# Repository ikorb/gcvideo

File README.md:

# GCVideo #

GCVideo is a small series of FPGA boards and VHDL projects
capable of converting the
GameCube's Digital Video port signals to standard video signals
without using the custom chip in the original component video cable.
There are currently VHDL projects for multiple FPGA boards, including
a Gamecube-to-DVI version for the KNJN Pluto IIx-HDMI and a
Gamecube-to-Component/RGB version for a board called GCVideo Lite
which is also documented in this repository.
GCVideo Lite has also been adapted to be used as
an RGB DAC for the Nintendo 64.

The schematics and layout are in the [Hardware](Hardware) directory
and the HDL projects are in the [HDL](HDL) directory. Each directory
should contain README.md files with further information.

## Mini-FAQ ##

1. I want one, how much is it?  
    I do not sell any hardware. Since this is an open-source project,
    other people will probably offer ready-made boards or modding
    services.

    GCVideo-DVI is based on a readily-available, commercial FPGA
    development board, so you could just buy that, flash it and
    install it yourself (or find someone to do it for you).

1. But why don't you just sell it?  
    Building hardware to be sold is a lot of work and requires much
    time that I'd rather use for something more
    interesting. Furthermore, the local laws require quite a bit of
    paperwork and investment to legally sell electronic devices that
    you build and I'd prefer not to deal with all of that.

1. You said your prototype came from OSHPark, so you have at least
    three boards. Can't you sell me one of them?  
    No, they're all accounted for already.

1. Why did you use that weird Video-DAC, it's a non-stock part at
    Digikey!<br>
    It wasn't when I designed the board some months ago... Instead it
    was the cheapest 24-bit video DAC available. It shouldn't be hard
    to adapt the design to a different DAC as long as it has 24 bit
    parallel input and a single-pumped clock. For YPbPr output, the
    DAC also needs to be able to generate a small offset on the Y line
    so that syncs can be generated below the blanking level.

1. Uh, it says XO2-256 in the schematic, but XO2-640 in the BOM. Which
    is the correct one?  
    The original plan was to use an XO2-256, but adding the color
    space conversion for RGB output increased the size of the design
    too much. It was left as an XO2-256 in the schematic to ensure
    only pins available on that chip are used, so a slightly cheaper
    Component-only version can be built.

1. What about line-doubling?  
    GCVideo Lite (the analog version) uses the smallest FPGA that
    could fit everything needed, but this chip does not have enough
    BlockRAM available to generate a line-doubled picture. It could be
    updated by using a larger, footprint-compatible FPGA, but since
    480i/576i are well-supported on component inputs and 240p/288p are
    rarely used by Gamecube titles this has not been attempted yet.

    GCVideo DVI fully supports line-doubling and can also overlay
    scanlines on the line-doubled picture if desired.

# Licence #

<pre>
Copyright (C) 2014-2021, Ingo Korb &lt;ingo@akana.de&gt;
All rights reserved.

Redistribution and use in source and binary forms, with or without
modification, are permitted provided that the following conditions are met:

1. Redistributions of source code must retain the above copyright notice,
   this list of conditions and the following disclaimer.
2. Redistributions in binary form must reproduce the above copyright notice,
   this list of conditions and the following disclaimer in the documentation
   and/or other materials provided with the distribution.

THIS SOFTWARE IS PROVIDED BY THE COPYRIGHT HOLDERS AND CONTRIBUTORS "AS IS"
AND ANY EXPRESS OR IMPLIED WARRANTIES, INCLUDING, BUT NOT LIMITED TO, THE
IMPLIED WARRANTIES OF MERCHANTABILITY AND FITNESS FOR A PARTICULAR PURPOSE
ARE DISCLAIMED. IN NO EVENT SHALL THE COPYRIGHT HOLDER OR CONTRIBUTORS BE
LIABLE FOR ANY DIRECT, INDIRECT, INCIDENTAL, SPECIAL, EXEMPLARY, OR
CONSEQUENTIAL DAMAGES (INCLUDING, BUT NOT LIMITED TO, PROCUREMENT OF
SUBSTITUTE GOODS OR SERVICES; LOSS OF USE, DATA, OR PROFITS; OR BUSINESS
INTERRUPTION) HOWEVER CAUSED AND ON ANY THEORY OF LIABILITY, WHETHER IN
CONTRACT, STRICT LIABILITY, OR TORT (INCLUDING NEGLIGENCE OR OTHERWISE)
ARISING IN ANY WAY OUT OF THE USE OF THIS SOFTWARE, EVEN IF ADVISED OF
THE POSSIBILITY OF SUCH DAMAGE.
</pre>

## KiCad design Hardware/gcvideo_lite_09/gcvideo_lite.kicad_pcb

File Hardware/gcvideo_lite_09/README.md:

# GCVideo Lite 0.9 #

This is the first prototype GCVideo Lite board with analog outputs in
RGB and Component/YPbPr formats, revision 0.9. This revision has a few
minor annoyances, but has proven to work.

## Connectors ##

The board has five connectors and one jumper: The main signal and
power input is the 11x2 connector P1 which connects to the GameCube
Digital Video port. The 6x1 connector on the side is the JTAG
connector which is needed to program the FPGA on the board. Signal
outputs are on the 5x1 and 4x1 connectors. There is also a 2x2
connector labelled "spare" next to the P1 and JTAG connectors which
at this time is mostly unused except for one pin that outputs an SPDIF
audio signal.

The single jumper on the board is located next to the JTAG connector
and consists of two solder pads. If these pads are bridged, the FPGA
will output RGB signals, if they are open it will output component
signals. 

### P1 (11x2) ###

The board is connected to the GameCube's digital video port using the
pins of the P1 connector. Since the original connector in the GameCube
is proprietary and no alternative is known, this needs to be done
using wires. It is strongly recommended to keep these wires as short
as possible since one of them is a 54MHz clock signal. Be absolutely
sure to not connect or bridge anything to pin 5 (+12V) - an accidental
short between that pin and any of the data lines will instantly fry
the Gamecube.

The pins of the P1 connector on the GCVideo Lite board correspond 1:1
with the pins of the GC's digital video connector, pin 1 is marked
with a square instead of a round pad. [This
site](http://gamesx.com/wiki/doku.php?id=av:nintendodigitalav) shows
the pin numbering directly on the connector. Alternatively, if you
look at the bottom of the GameCube's main PCB with the video
connectors facing away from you, pin 1 of the DV connector should be
the bottom right pin, pin 2 the one above it. There are also numbers
for the outermost pins marked besides the connector on the top side.

I have no idea what your options are if you have a later-model
GameCube where Nintendo removed the digital AV port.

### JTAG (6x1) ###

The FPGA has an internal configuration memory which is blank when it
is delivered from the factory. To program the FPGA, you need a
JTAG interface suitable for use with Lattice's software - I use a
clone of the HW-USBN-2A cable, but the software also supports a
parallel port cable (no idea about the pinout) or FT2232D-based USB
devices (look for Lattice application note AN8082 for the schematic).

On the software side, the FPGA can be programmed using the Lattice
Diamond software package. Although it may appear a bit large at about
1.5 GByte download size, this is quite small compared to similar
packages from other FPGA vendors. ;)
If programming the internal configuration flash of the XO2 fails, try
the .jed file instead of the .bit file.

### Video (5x1) ###

The video output connector is the 5x1 connector on the side of the
board. Pin 1 is marked using a square instead of a round pad and
outputs the R (RGB) or Pr (Component, red plug) signal. Pins 2 and 4
are ground pins. Pin 3 (the middle one) outputs the G (RGB) or Y
(Component, green plug) signal, Pin 5 outputs the B (RGB) or Pb
(Component, blue plug) signal. There is also a tiny label hidden
between the resistors and capacitors saying "B-G-R" which uses "-" as
a shorthand for ground.

### Sync (4x1) ###

The GCVideo Lite board has a dedicated connector for sync signals. You
can ignore it if you only want to output Component video, but it is
required if you want to use RGB. The pins are labelled "C V H -" on
the sikscreen. The "-" pin is ground, "V" and "H" are vertical and
horizontal sync signals and "C" is a composite sync signal. The
composite sync signal should be directly usable e.g. for connections
to SCART televisions or scalers like an XRGB Mini that need a
composite sync while the V- and H-Sync signals can be used for VGA
inputs - but remember that the GameCube outputs 15kHz video during
startup and not every game supports 480p!

While the hardware could support RGB with Sync-on-Green, this is
currently not implemented.

### Spare (2x2) ###

The 2x2 pin group marked "Spare" in the corner of the group is unused
except for the square pin next to P1. This pin is used to output an
SPDIF audio signal. For more information on interfacing this signal to
an SPDIF receiver, please check the [README.md of the gcvideo_lite HDL
project](../../HDL/gcvideo_lite/README.md).

Please do not connect this pin directly to a coaxial SPDIF input, the
feature was added after the board was designed and there is no
protection on this pin.

## Building ##

The PCB uses four layers, so it is not suitable for etching at home,
but there are many prototyping services available that offer small
runs of a PCB. The prototype has been ordered from
[OSHPark](http://www.oshpark.com) and the zip file with the data they
require has been included in the repository.

The values of the parts are marked within their footprint in rather
tiny letters, alternatively you can look at the [BOM.csv](BOM.csv)
file for the value corresponding to each of the component references.

## Audio ##

There are currently two options for the audio signal from the Gamecube
when GCVideo Lite is used as the video encoder. The first option is to
use the audio signals from the analog AV port as usual. The second
option is to use the SPDIF encoder implemented in GCVideo Lite. The
[README.md of the gcvideo_lite HDL
project](../../HDL/gcvideo_lite/README.md) has more information about
connecting this signal - since it was added after the board was
designed, no protection is present on the signal and a direct
connection to an SPDIF input may destroy the FPGA.

## Known issues ##

* The drill holes for the JTAG and output video/sync connectors are
    slightly too small to fit standard 2.54mm pitch pin headers.
* The pads of the two ICs (from KiCADs standard footprint library) are
    meant for reflow soldering, not hand soldering. It is still
    possdo not need to use ible to hand-solder these chips, but it takes a lot of
    patience.
* The "component cable connected" pin is always active, which causes
    some homebrew applications to switch into 480p mode by
    default. This can be problematic for users of SD-only monitors,
    but since the board must be connected to the cube using wires
    anyway, leaving out the connection of pin 1 (or adding a switch in
    that line) can fix this issue.
* Trace width could be increased for some of the supply traces on the
    top and bottom layers.
* Vias are a bit large-ish.

## Other Systems ##

With a different program in the FPGA it is be possible to use the
same board to provide RGB and/or Component outputs for an N64, see
the [gcvideo_lite_n64](../gcvideo_lite_n64/README.md) directory for
details.

Measurements on a Wii board indicate that thare is an internal video
data bus that may use the same signals as the GameCube's digital video
port, but since the Wii already supports Component video natively
there isn't much reason to actually use this board on a Wii. It may
need some hardware changes as the Wii uses 1.8V signal levels instead
of the 3.3V seen on a GameCube.

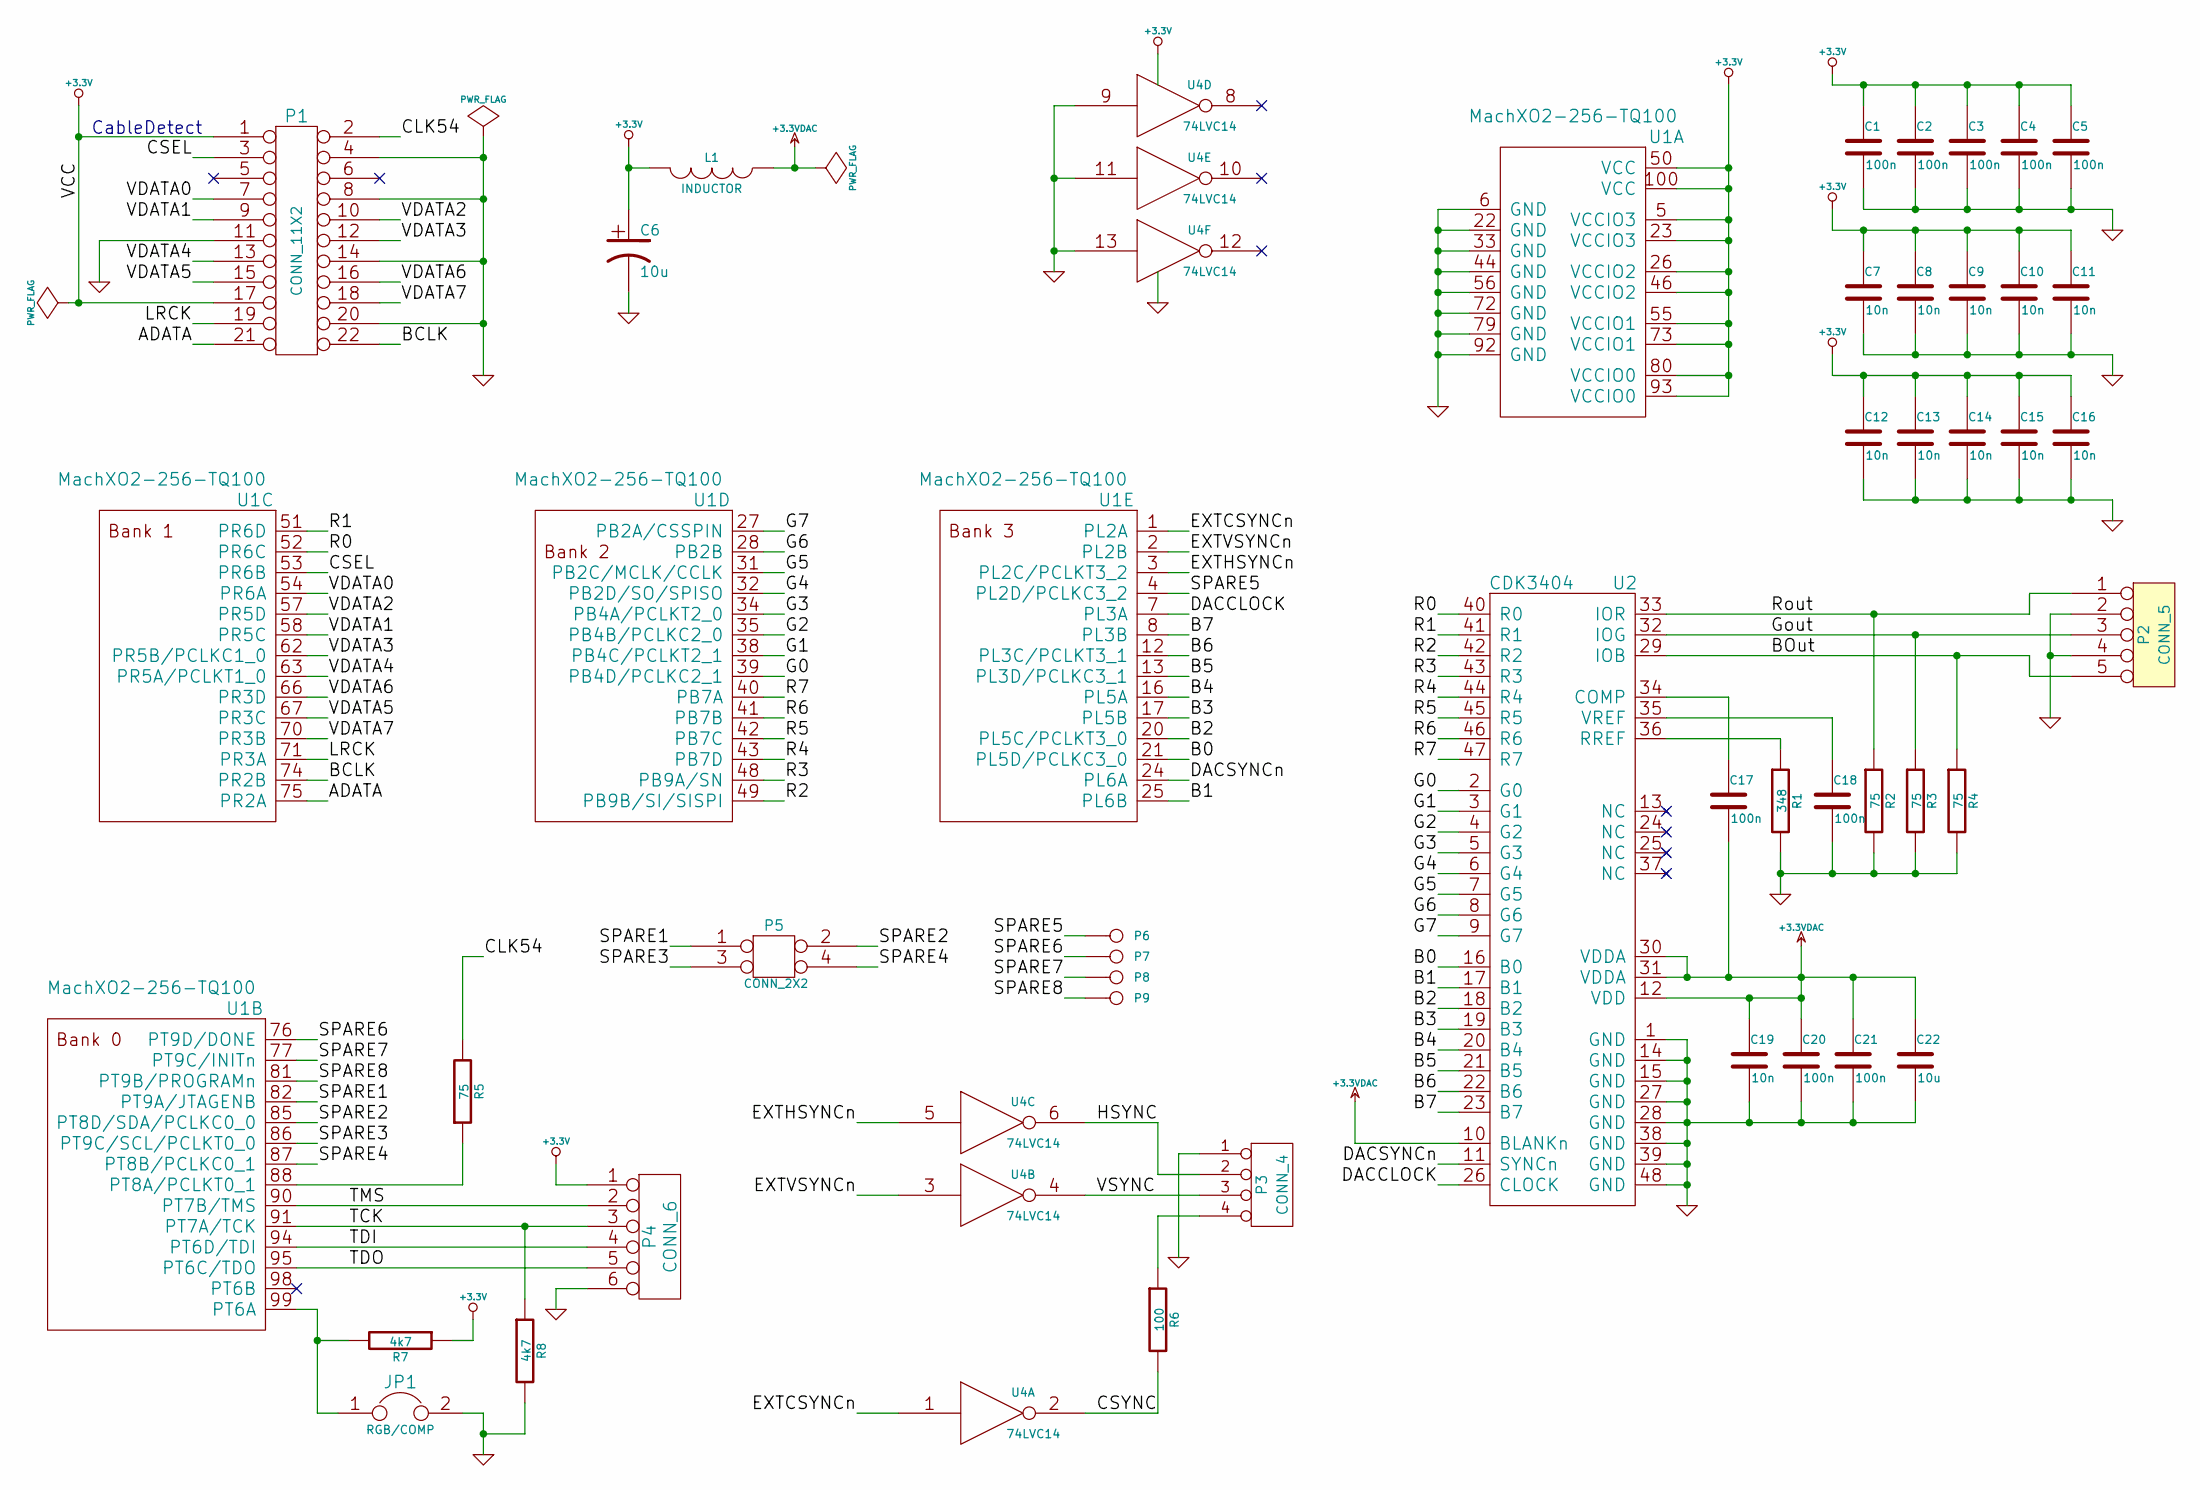
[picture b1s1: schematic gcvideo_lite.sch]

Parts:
C1, C2, C3, C4, C5, C17, C18, C20, C21: 100n
C6, C22: 10u
C7, C8, C9, C10, C11, C12, C13, C14, C15, C16, C19: 10n
JP1: RGB/COMP
L1: INDUCTOR
P1: CONN_11X2
P2: CONN_5
P3: CONN_4
P4: CONN_6
P5: CONN_2X2
P6, P7, P8, P9: CONN_1
R1: 348
R2, R3, R4, R5: 75
R6: 100
R7, R8: 4k7
U1: MachXO2-256-TQ100
U2: CDK3404
U4: 74LVC14

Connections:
+3.3V: C1.1, C2.1, C3.1, C4.1, C5.1, C6.1, C7.1, C8.1, C9.1, C10.1, C11.1, C12.1, C13.1, C14.1, C15.1, C16.1, L1.2, P1.1, P1.17, P4.1, R7.1, U1.5 (VCCIO3), U1.23 (VCCIO3), U1.26 (VCCIO2), U1.46 (VCCIO2), U1.50 (VCC), U1.55 (VCCIO1), U1.73 (VCCIO1), U1.80 (VCCIO0), U1.93 (VCCIO0), U1.100 (VCC), U4.14 (VCC)
+3.3VDAC: C17.2, C19.1, C20.1, C21.1, C22.1, L1.1, U2.10 (BLANKn), U2.12 (VDD), U2.30 (VDDA), U2.31 (VDDA)
/ADATA: P1.21, U1.75 (PR2A)
/B0: U1.21 (PL5D/PCLKC3_0), U2.16 (B0)
/B1: U1.25 (PL6B), U2.17 (B1)
/B2: U1.20 (PL5C/PCLKT3_0), U2.18 (B2)
/B3: U1.17 (PL5B), U2.19 (B3)
/B4: U1.16 (PL5A), U2.20 (B4)
/B5: U1.13 (PL3D/PCLKC3_1), U2.21 (B5)
/B6: U1.12 (PL3C/PCLKT3_1), U2.22 (B6)
/B7: U1.8 (PL3B), U2.23 (B7)
/BCLK: P1.22, U1.74 (PR2B)
/BOut: P2.5, R4.1, U2.29 (IOB)
/CLK54: P1.2, R5.2
/CSEL: P1.3, U1.53 (PR6B)
/CSYNC: R6.2, U4.2
/DACCLOCK: U1.7 (PL3A), U2.26 (CLOCK)
/DACSYNCn: U1.24 (PL6A), U2.11 (SYNCn)
/EXTCSYNCn: U1.1 (PL2A), U4.1
/EXTHSYNCn: U1.3 (PL2C/PCLKT3_2), U4.5
/EXTVSYNCn: U1.2 (PL2B), U4.3
/G0: U1.39 (PB4D/PCLKC2_1), U2.2 (G0)
/G1: U1.38 (PB4C/PCLKT2_1), U2.3 (G1)
/G2: U1.35 (PB4B/PCLKC2_0), U2.4 (G2)
/G3: U1.34 (PB4A/PCLKT2_0), U2.5 (G3)
/G4: U1.32 (PB2D/SO/SPISO), U2.6 (G4)
/G5: U1.31 (PB2C/MCLK/CCLK), U2.7 (G5)
/G6: U1.28 (PB2B), U2.8 (G6)
/G7: U1.27 (PB2A/CSSPIN), U2.9 (G7)
/Gout: P2.3, R3.1, U2.32 (IOG)
/HSYNC: P3.2, U4.6
/LRCK: P1.19, U1.71 (PR3A)
/R0: U1.52 (PR6C), U2.40 (R0)
/R1: U1.51 (PR6D), U2.41 (R1)
/R2: U1.49 (PB9B/SI/SISPI), U2.42 (R2)
/R3: U1.48 (PB9A/SN), U2.43 (R3)
/R4: U1.43 (PB7D), U2.44 (R4)
/R5: U1.42 (PB7C), U2.45 (R5)
/R6: U1.41 (PB7B), U2.46 (R6)
/R7: U1.40 (PB7A), U2.47 (R7)
/Rout: P2.1, R2.1, U2.33 (IOR)
/SPARE1: P5.1, U1.82 (PT9A/JTAGENB)
/SPARE2: P5.2, U1.85 (PT8D/SDA/PCLKC0_0)
/SPARE3: P5.3, U1.86 (PT9C/SCL/PCLKT0_0)
/SPARE4: P5.4, U1.87 (PT8B/PCLKC0_1)
/SPARE5: P6.1, U1.4 (PL2D/PCLKC3_2)
/SPARE6: P7.1, U1.76 (PT9D/DONE)
/SPARE7: P8.1, U1.77 (PT9C/INITn)
/SPARE8: P9.1, U1.81 (PT9B/PROGRAMn)
/TCK: P4.3, R8.1, U1.91 (PT7A/TCK)
/TDI: P4.4, U1.94 (PT6D/TDI)
/TDO: P4.5, U1.95 (PT6C/TDO)
/TMS: P4.2, U1.90 (PT7B/TMS)
/VDATA0: P1.7, U1.54 (PR6A)
/VDATA1: P1.9, U1.58 (PR5C)
/VDATA2: P1.10, U1.57 (PR5D)
/VDATA3: P1.12, U1.62 (PR5B/PCLKC1_0)
/VDATA4: P1.13, U1.63 (PR5A/PCLKT1_0)
/VDATA5: P1.15, U1.67 (PR3C)
/VDATA6: P1.16, U1.66 (PR3D)
/VDATA7: P1.18, U1.70 (PR3B)
/VSYNC: P3.3, U4.4
GND: C1.2, C2.2, C3.2, C4.2, C5.2, C6.2, C7.2, C8.2, C9.2, C10.2, C11.2, C12.2, C13.2, C14.2, C15.2, C16.2, C18.2, C19.2, C20.2, C21.2, C22.2, JP1.2, P1.4, P1.8, P1.11, P1.14, P1.20, P2.2, P2.4, P3.1, P4.6, R1.2, R2.2, R3.2, R4.2, R8.2, U1.6 (GND), U1.22 (GND), U1.33 (GND), U1.44 (GND), U1.56 (GND), U1.72 (GND), U1.79 (GND), U1.92 (GND), U2.1 (GND), U2.14 (GND), U2.15 (GND), U2.27 (GND), U2.28 (GND), U2.38 (GND), U2.39 (GND), U2.48 (GND), U4.7 (GND), U4.9, U4.11, U4.13
unnamed: C17.1, U2.34 (COMP)
unnamed: C18.1, U2.35 (VREF)
unnamed: JP1.1, R7.2, U1.99 (PT6A)
unnamed: P3.4, R6.1
unnamed: R1.1, U2.36 (RREF)
unnamed: R5.1, U1.88 (PT8A/PCLKT0_1)

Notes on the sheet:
CableDetect

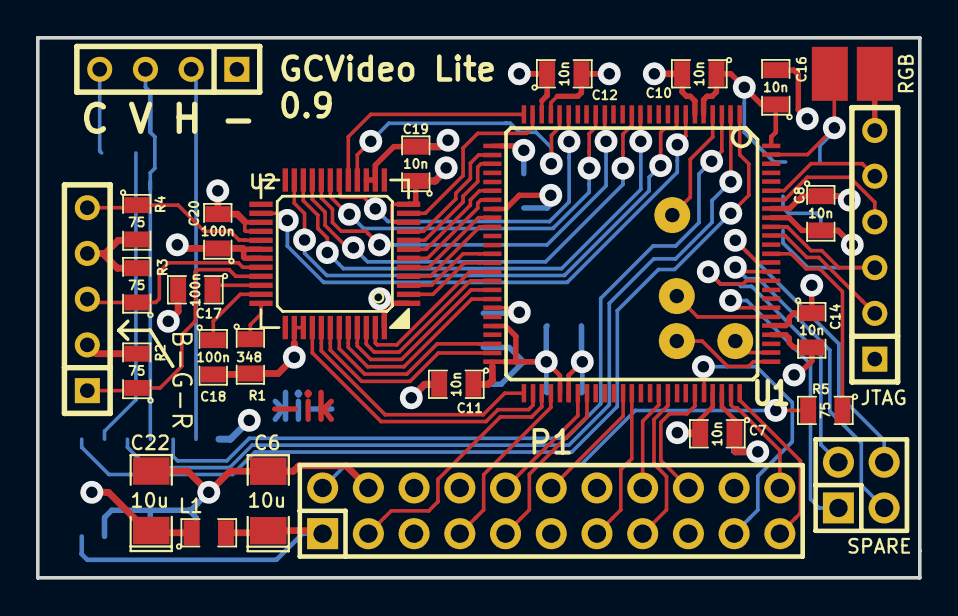
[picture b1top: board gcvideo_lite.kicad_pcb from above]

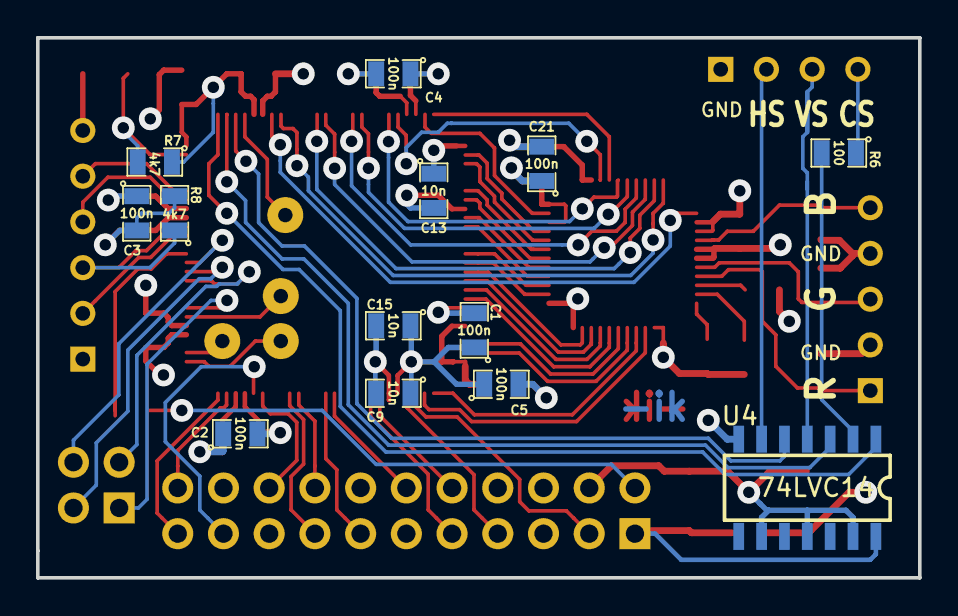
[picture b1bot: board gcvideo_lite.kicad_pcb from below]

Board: 4 copper layers, 49.0 x 30.0 mm, 44 parts (13 on the bottom side), 69 nets.

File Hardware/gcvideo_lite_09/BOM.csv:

Id	Designator	Package	Quantity	Designation	Digikey part no	Notes
1	C1,C2,C3,C4,C5,C17,C18,C20,C21	SMD_Packages:SM0805	9	100n	399-1170-1-ND	or any other 100nF 0805 capacitor rated at least 6.3V
2	C6,C22	SMD_Packages:SM1206POL	2	10u	479-8151-1-ND	or similar (rated at least 6.3V)
3	C9,C7,C8,C10,C11,C12,C13,C14,C15,C16,C19	SMD_Packages:SM0805	11	10n	399-1159-1-ND	or any other 100nF 0805 capacitor rated at least 6.3V
4	JP1	SOLDER_JUMPER:SOLDER_JUMPER	1	RGB/COMP	-	
5	L1	SMD_Packages:SM0805	1	INDUCTOR	1276-6349-1-ND	Decouples DAC supply from FPGA supply, can be replaced with piece of wire in emergencies
6	P1	Pin_Headers:Pin_Header_Straight_2x11	1	CONN_11X2	-	
7	P2	Connect:SIL-5	1	CONN_5	-	
8	P3	Connect:SIL-4	1	CONN_4	-	
9	P4	Connect:SIL-6	1	CONN_6	-	
10	P5	Pin_Headers:Pin_Header_Straight_2x02	1	CONN_2X2	-	
11	P6,P7,P8,P9	Wire_Pads:SolderWirePad_single_0-8mmDrill	4	CONN_1	-	
12	R1	SMD_Packages:SM0805	1	348	311-348CRCT-ND	Can be replaced with stacked 390 and 3900 Ohm resistors if necessary
13	R2,R3,R4,R5	SMD_Packages:SM0805	4	75	311-75ARCT-ND	or any other 75 ohm 0805 resistor
14	R6	SMD_Packages:SM0805	1	100	311-100CRCT-ND	or any other 50-200 ohm 0805 resistor  just a cautionary device on the Csync line
15	R7,R8	SMD_Packages:SM0805	2	4k7	311-4.70KCRCT-ND	or any other 1k-10k ohm 0805 resistor (pullups/pulldowns)
16	U1	SMD_Packages:TQFP_100	1	MachXO2-640-TQ100	220-1492-ND	It's still an XO2-256 in the schematic, but an XO2-640 is required!
17	U2	Housings_QFP:lqfp-48	1	CDK3404	1016-1935-ND 	
18	U4	Housings_SOIC:SOIC-14_Narrow	1	74LVC14	296-1699-1-ND	
						
						
	Warning: Part numbers for resistors and capacitors have not been checked!

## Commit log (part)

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2014-08-31 Import initial release
2014-09-11 Optimize YCbCr to RGB conversion
    Optimize the YCbCr to RGB conversion by clocking it at twice the pixel
    rate so intermediate registers can be reused from odd to even
    conversion stages.
2014-09-21 Fix project description in gcvl64 copyright headers
2014-12-03 Add Artemio (240p test suite) to credits
    Mention the 240p test suite from Artemio in the credits section.
2015-01-10 Add SPDIF output for GCVideo Lite
    Add an SPDIF output for GCVideo Lite (Gamecube only) and update
    various pieces of documentation to mention it where appropiate.
2015-04-04 Add SPDIF and on-screen display to DVI version
2015-06-06 Improve SPDIF compatibility
    Set the "copy allowed" bit in the SPDIF channel status to improve
    compatibiltiy.
2015-08-18 Remove trailing whitespace from VHDL sources
2015-08-21 GCVideo-DVI Version 2.0
2015-11-22 gcvideo-dvi: Add volume control
    Add a (decrease-only) volume control in the OSD
2016-03-04 crt0: Remove code from comments
2016-03-05 GCVideo DVI: Add build for Shuriken Video v3/v4 boards
2016-06-21 Update firmware Makefile with correct bitstream paths
    Update the bitstream paths in the firmware Makefile to point to the
    build directory, not the src directory.
2016-06-21 Reduce size of infoframe ROM
    Optimize the layout of the infoframe ROM by reducing redundancies and
    changing the address sequencing to match the new layout. This change
    also allows the inclusion of an alternate ACR packet for 48000Hz audio.
2016-08-12 Update audio subsystem for Wii
    Add the necessary updates to the audio subsystem for the Wii:
    - use 384*f_s instead of 128*f_s for more reliable I2S decoding
    (the Wii uses a 64*f_s bit clock, reading that with a jittering
    128*f_s logic clock is unreliable)
    - switch between 48000 and 48042 Hz sample rate depending on the
    console mode
2016-08-12 Bump GCVideo-DVI version number to 2.2
    Bumb the GCVideo-DVI version number in both relevant Makefiles to 2.2
    for a future release
2016-08-12 Fix item marker not showing on decimal values
    Fix the missing item marker not showing up when a decimal value is
    selected by moving it one character further to the left.
2016-08-14 Add IR remote control capability
    Add all the infrastructure for decoding IR remotes using the NEC
    protocol to add an alternative way of controlling the OSD in case a
    Gamecube pad is not available/practical.
2016-08-14 Add .bit files for release 2.2
    Add the .bit files for the four builds that were accidentally left out
    of the 2.2 tagged commit.
2016-09-20 Define IR receiver+button pins for Shuriken Video
    Add IR receiver capability to the two Shuriken Video boards.
2016-09-20 Update NEWS file
    Oops, I completely forgot that this repository has a NEWS file at its
    root. Finally updated for the current release.
2016-12-29 GCVideo-DVI: Add Wii builds for both shuriken boards
2017-09-10 Call firmware makefile from HDL makefile to build correct firmware version
2017-09-19 Add a logo to the main menu
2017-09-19 Implement a better heartbeat pattern
    Improve the heartbeat LED patterns of GCVideo-DVI by basing it both on
    the main clock and VSync. The patterns are chosen so one can be used
    to invert the other to derive a useful single-LED pattern.
2017-09-19 Fix int8_t definition
2017-09-21 Add a -128..127 signed byte value type for OSD menus
2017-10-03 Firmware: Use a plus sign for positive values of type SBYTE_127
    Force a plus sign for positive but non-zero values for type SBYTE_127
    so the entries in the picture settings menu are shown with +/- signs
    if they are set to a non-neutral value.
2017-10-03 Bump GCVideo-DVI version number to 2.4
2017-10-22 Add section about 3d printed mount
2017-12-10 HDL/README.md: Update comment about Shuriken version
2017-12-10 Bump GCVideo-DVI version number to 2.4a
2019-05-31 backport chroma mixing fix for Cr-first lines
2020-01-13 fix calculation of settings slot when storing settings
    Fix the calculation of the correct settings slot when storing
    settings, avoids various nasty flash corruption problems.
2020-01-13 add note about analog output in YPbPr mode and picture controls
2020-01-19 enable wait-for-DCM-lock in bitgenconfig
    Delay FPGA startup until the DCMs are locked, which appears to help
    with ICAP access issues on some Wiis.
2020-01-19 Change the GCDual/WiiDual heartbeat to VSync only
    Make the WiiDual version buildable again by changing the heartbeat
    blink source to the VSync-only signal.
2020-01-20 Fix disable-logic on mode change
    Fix the logic for temporarily disabling the output on mode changes to
    ensure that it always counts down the frame counter even if the
    console switches back to the previous mode before the intended number
    of disable frames is reached.
2020-01-28 flasher: fix handling of uncompressed chunks
2020-02-02 Add GCplug build configuration to GCVideo-DVI
2020-02-02 show version in main flasher screen
2020-05-21 updater: Generate faint white noise when update data is shown
    Generate a very faint white noise in the background while the update
    data is shown to ensure that there is traffic on the ADATA
    signal. This ensures that the diagnostics mode of the flasher does not
    show "missing or silence" anymore while the other signals are shown as OK.
2020-05-21 Package Wii updater.dol for Homebrew Channel
    Create a zip file containing the Wii updater in a layout that can
    directly be used with the Homebrew Channel for improved user experience.
2020-05-21 bump GCVideo-DVI version number to 3.0e
2020-06-13 Only build the Regenerate CSync menu entry for DUAL hardware
    On GCVideo hardware without an analog video output option, the
    "Regenerate CSync" option has no effect, so don't build the menu
    entry in the corresponding build configuration, making the menu a
    bit more tidy (analogous to Output settings->Analog output).
2020-11-28 deprecate Pluto board for end-users
2020-12-01 screen_mainmenu: Shrink vertical size of menu
    Shrink the vertical size of the main menu by overlapping the in/out
    resolution listing with the "Exit" menu entry.
2020-12-01 make the border around the IR config menu optional
    Add a parameter to the IR config menu to optionally leave out drawing
    of the border around the menu so it can be embedded in an existing screen.
2020-12-01 add a flash memory hex viewer to the flasher
    Add a hex viewer for the flash memory to the flash update tool for
    easier remote debugging in case of problems.
2020-12-01 Blanking_Regenerator_Fixed: Ensure nominal length of sync pulses
    Regenerate the sync signals with their nominal lengths according to
    CEA, fixes some issues (Cr/Cb swap, flaky signal recognition) I
    observed with a cheap HDMI/SDI converter.
2020-12-01 reduce screen_irconfig size
    Optimize the size of screen_irconfig by removing the debug mode and
    implementing the button list in a more space-efficient way.
2020-12-01 Use table-based scanline profiles instead of a strength setting
    Switch the scanline settings from a simple strength value to a
    table-based system that uses the pixel luma to determine scanline
    strength. The new implementation offers three profiles (plus "off") to
    cover multiple use cases and because that happens to be a convenient
    amount to store in BRAM or config flash.
2020-12-01 Move some parts of the code into the module "main"
    Strategically move parts of the code into a module called "main".
2020-12-01 Add non-standard mode detection
    Add detection of non-standard video modes.
2020-12-01 menu.c: Change definition of line in menuitem_t
    Modify the meaning of the item entry in a menuitem_t to refer to the
    offset relative to the menu's Y coordinate instead of making it
    relative to the menu's drawing area. This effectively moves a few
    runtime "+ 1" from the menu code to static constants for the menuitems.
2020-12-01 osd: remove osd_puthex
    Remove the (unused) osd_puthex function.
2020-12-01 move mainloop to screen_idle.c
    Move the main loop from main.c to screen_idle.c
2020-12-01 ZPU_DPRAM: Add option to preset contents
    Add a generic to the ZPU_DPRAM module that can be used to specify
    preset contents for the DPRAM's memory array.
2020-12-01 increase config rate in generated bitstream
    Increase the config rate parameter in the bitstream from 1 to 17
    (approximately MHz) to reduce the startup time.
2020-12-01 add scripts for adding information tags to the bitstreams
    Drop in two Perl scripts that add version+checksum information tags to
    the compiled bitstreams.
2020-12-01 osd: export chars per line and lines on screen macros
    Add an OSD_ prefix to the CHARS_PER_LINE and LINES_ON_SCREEN macros
    and make them public in osd.h.
2020-12-01 add an option to disable chroma interpolation
    Add an option to disable the chroma interpolation in the
    4:2:2-to-4:4:4 interpolation stage for people who prefer the resulting
    color shift.
2020-12-01 add a flasher module
    Add a second module called "flasher" to the system for the firmware
    update process, not functional yet.
2020-12-01 add scripts to build a firmware updater from individual binaries
    Add two scripts to build all versions of the firmware and combine them
    into ready-to-run updaters for Gamecube/Wii.
2020-12-01 clear entire screen to remove resolution popup from screen
    Clear the entire screen instead of trying to just blank out the
    resolution popup to save a bit of space.
2020-12-01 make ZPU dual-port RAM port B reads one cycle faster
    Remove an unneccessary buffering of the port B address to make
    dual-port RAM reads on that port one clock cycle faster.
2020-12-01 update constraints for Wii-Dual board
    Update the pin assignments for the Wii-Dual board to the ones used (as
    far as I know) by the actual release boards.
2020-12-01 Remove obsolete FIXME comment from pad.c
    Remove an old FIXME comment in pad.c.
2020-12-01 Remove gcvideo_dvi_p2xh symlink
    Remove the gcvideo_dvi_p2xh symlink, it's been long enough.
2020-12-01 Simplify heartbeat pattern implementation
    Simplify the implementation of the heartbeat pattern, may or may not
    save some FPGA resources.
2020-12-01 Rename "Other settings" to "Output settings"
    Rename the "Other settings" menu to "Output settings" as better
    reflects its contents.
2021-10-16 Modify infoframe for better compatibility
    Improve compatibility with Samsung C7000 series TVs by removing a bit
    from the infoframe that is not strictly needed. With the previous
    infoframe, these TVs would fail to show a picture after certain
    interlaced-to-progressive mode switches until the cable was physically
    re-plugged.
2021-10-16 various size optimizations
    Free up a bit of space by optimizing various pieces of code.
2021-10-16 Use title caps in menus
    Update the menu screens to use Title Caps for everything instead of an
    inconsistent mixture of Title Caps and First word caps.
2022-02-17 Corrected error in Makefile
2022-02-22 Working on simple LED heartbeat.
2022-02-22 Trying to slow down the blink rate. With 119, it was blinking ~231kHz
